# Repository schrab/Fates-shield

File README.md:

# Fates shield DAC board for Raspberry Pi

Monome [Fates](https://github.com/okyeron/fates) with MIDI and onboard microphone in Monome Shield form-factor

### Specs:

- WM8731 stereo audio codec with headphone driver
- Microphone
- ZJYM270-7PV2.0 SSD1325 128x64 OLED display (NHD-2.7-12864WDW3 alternative [from Aliexpress](https://aliexpress.ru/item/4000265549668.html))
  
- 3 pushbuttons
- 4 rotary encoders
- 2x 1/8in inputs
- 2x 1/8in outputs
- 1/8in stereo headphone out
- 1/8in UART MIDI in/out

###TODO
  
- [X] Fix upper OLED holes position
- [ ] Add RC filtering for encoders and keys
- [ ] Fix headphone jack hole
- [X] Fix swapped MIDI IN lines
- [X] Fix MIDI OUT buffer lines

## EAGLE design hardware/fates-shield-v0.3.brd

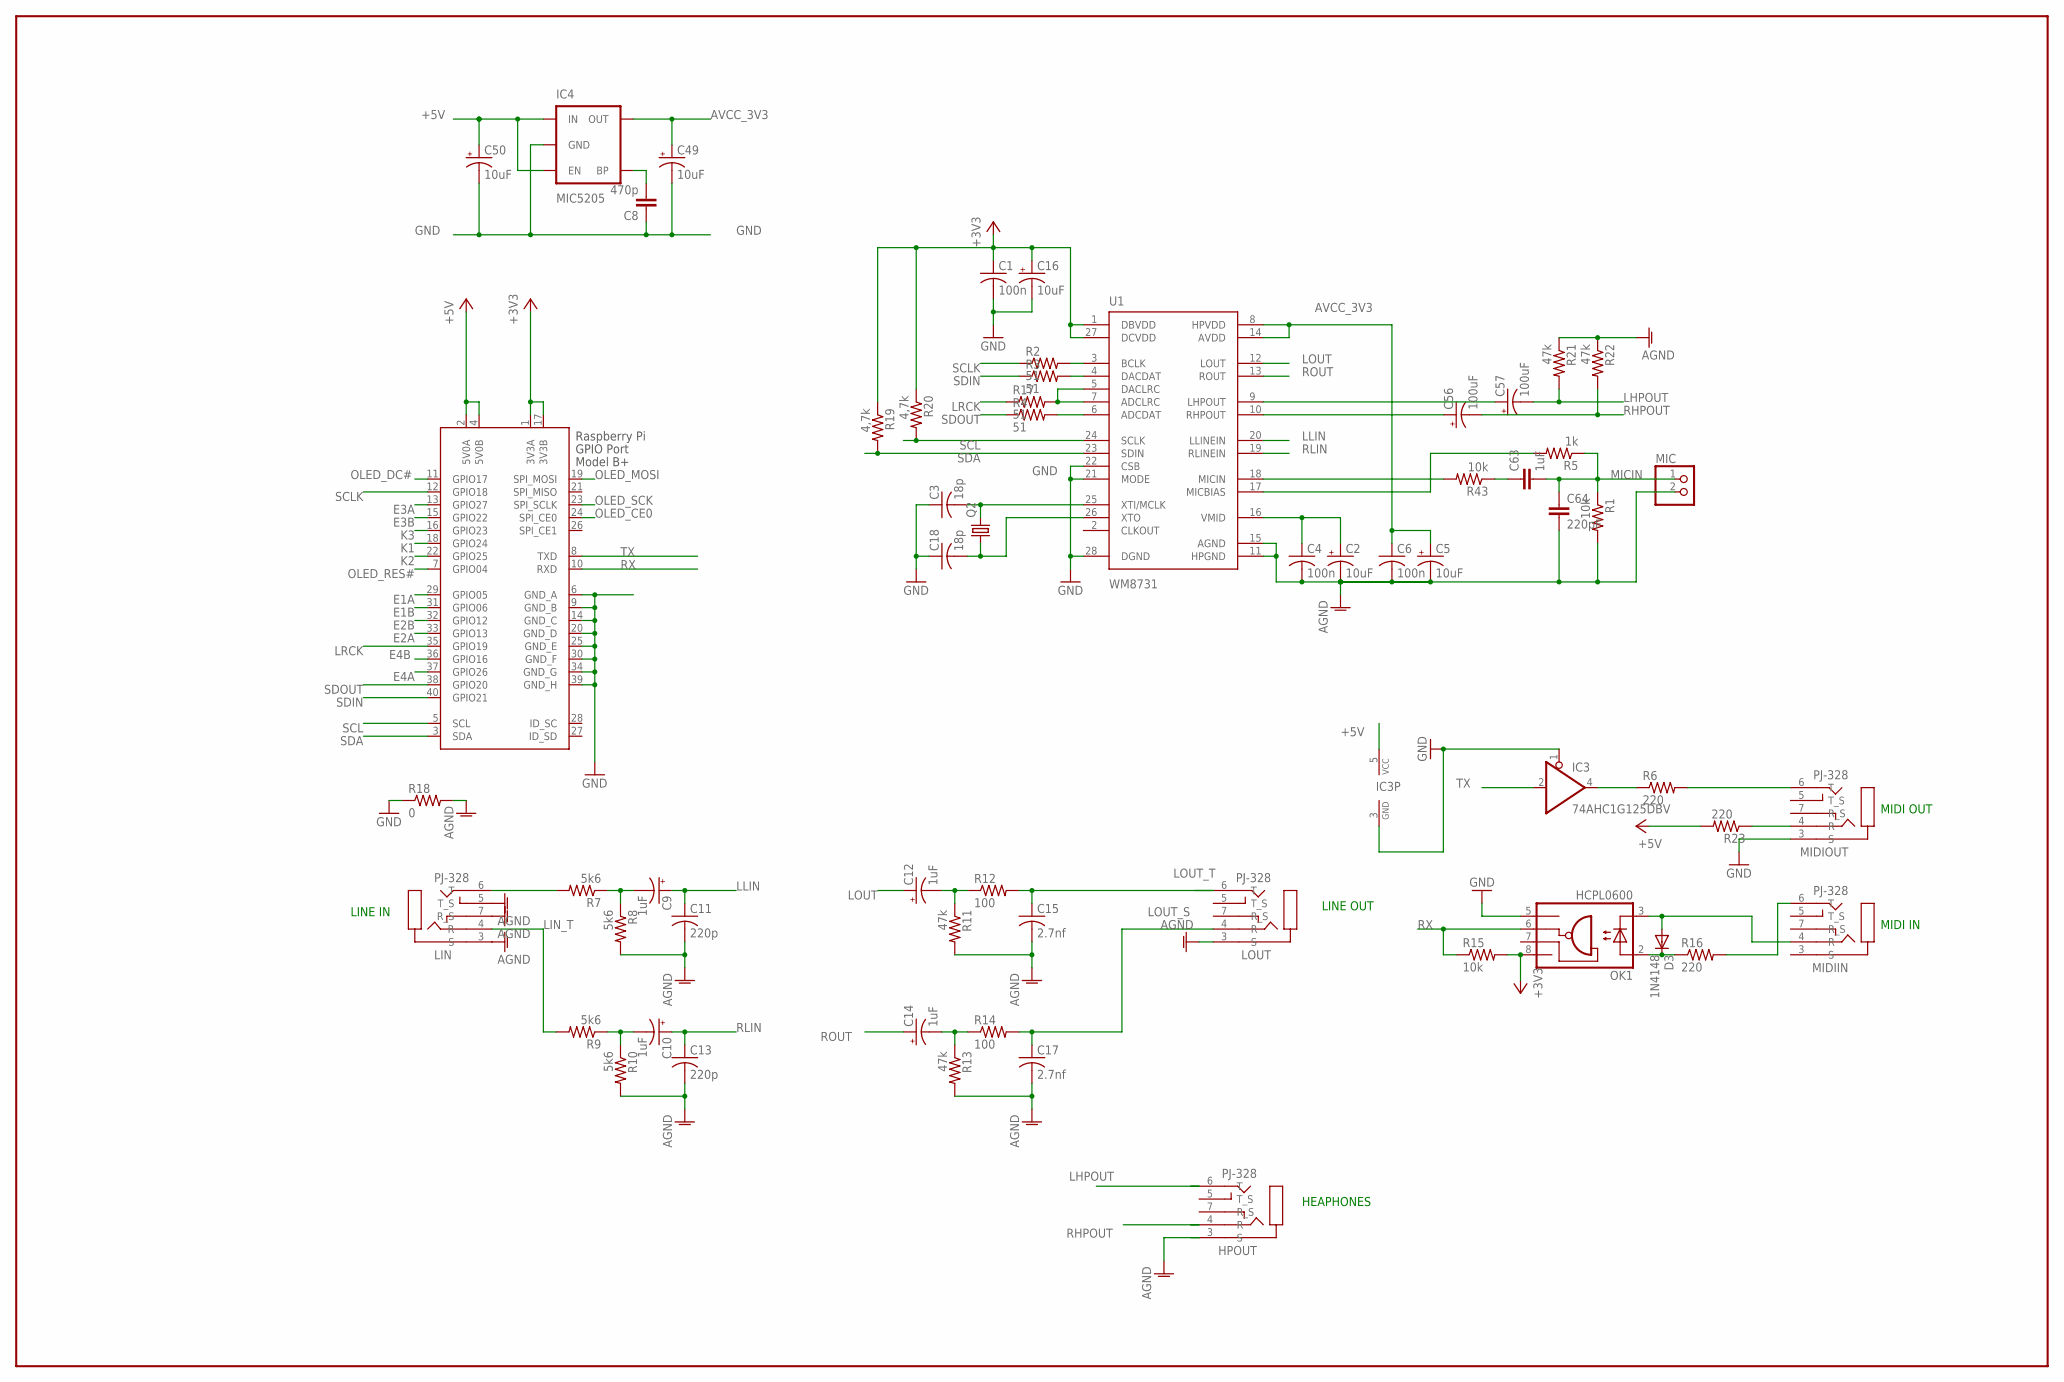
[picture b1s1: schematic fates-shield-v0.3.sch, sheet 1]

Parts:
C1, C4, C6: 100n; C0603
C2, C5, C16, C49, C50: 10uF; EIA3216
C3, C18: 18p; C0603
C8: 470p; 0603-CAP
C9, C10, C12, C14: 1uF; EIA3216
C11, C13: 220p; C0603
C15, C17: 2.7nf; C0603
C56, C57: 100uF; EIA3528
C63: 1uF; 0603-CAP
C64: 220pF; 0603-CAP
D3: 1N4148; SOD323-W
HPOUT: PJ-328; PJ328
IC3: 74AHC1G125DBV; DBV_R-PDSO-G5
IC4: MIC5205; SPARKFUN-3-2-07_SOT23-5
LIN: PJ-328; PJ328
LOUT: PJ-328; PJ328
MIC: PINHD-1X2; 1X02
MIDIIN: PJ-328; PJ328
MIDIOUT: PJ-328; PJ328
OK1: HCPL0600; SOIC08
Q2: CRYSTALHC49UP; HC49UP
R1, R43: 10k; 0603-RES
R2, R3, R4, R17: 51; R0603
R5: 1k; 0603-RES
R6, R16, R23: 220; R0603
R7, R8, R9, R10: 5k6; R0603
R11, R13: 47k; R0603
R12, R14: 100; R0603
R15: 10k; R0603
R18: 0; R0603
R19, R20: 4,7k; 0603-RES
R21, R22: 47k; 0603-RES
U1: WM8731; SSOP28
X1: RASPI_BOARD_B+#_E3; RASPI_BOARD_B+_EDGES_3DRILL

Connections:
+3V3: C1.1, C16.A (+), OK1.8 (VCC), R15.2, R19.1, R20.1, U1.1 (DBVDD), U1.27 (DCVDD), X1.1 (3V3A), X1.17 (3V3B); also elsewhere on the board
+5V: C50.A (+), IC3.5 (VCC), IC4.1 (IN), IC4.3 (EN), R23.2, X1.2 (5V0A), X1.4 (5V0B)
ADCDAT: R4.2, U1.6 (ADCDAT)
ADCLRC: R17.2, U1.5 (DACLRC), U1.7 (ADCLRC)
AGND: C2.C (-), C4.2, C5.C (-), C6.2, C11.2, C13.2, C15.2, C17.2, C64.2, HPOUT.3 (S), LIN.3 (S), LIN.5 (T_S), LIN.7 (R_S), LOUT.3 (S), MIC.2, R1.2, R8.2, R10.2, R11.2, R13.2, R18.2, R21.1, R22.1, U1.11 (HPGND), U1.15 (AGND)
AVCC_3V3: C5.A (+), C6.1, C49.A (+), IC4.5 (OUT), U1.8 (HPVDD), U1.14 (AVDD)
BCLK: R2.2, U1.3 (BCLK)
DACDAT: R3.2, U1.4 (DACDAT)
E1A: X1.29 (GPIO05); also elsewhere on the board
E1B: X1.31 (GPIO06); also elsewhere on the board
E2A: X1.33 (GPIO13); also elsewhere on the board
E2B: X1.32 (GPIO12); also elsewhere on the board
E3A: X1.13 (GPIO27); also elsewhere on the board
E3B: X1.15 (GPIO22); also elsewhere on the board
E4A: X1.37 (GPIO26); also elsewhere on the board
E4B: X1.36 (GPIO16); also elsewhere on the board
GND: C1.2, C3.1, C8.1, C16.C (-), C18.1, C49.C (-), C50.C (-), IC3.1 (OE), IC3.3 (GND), IC4.2 (GND), MIDIOUT.3 (S), OK1.5 (GND), R18.1, U1.21 (MODE), U1.22 (CSB), U1.28 (DGND), X1.6 (GND_A), X1.9 (GND_B), X1.14 (GND_C), X1.20 (GND_D), X1.25 (GND_E), X1.30 (GND_F), X1.34 (GND_G), X1.39 (GND_H); also elsewhere on the board
K1: X1.18 (GPIO24); also elsewhere on the board
K2: X1.22 (GPIO25); also elsewhere on the board
K3: X1.16 (GPIO23); also elsewhere on the board
LHPOUT: C57.C (-), HPOUT.6 (T), R21.2
LIN_T: LIN.4 (R), R9.2
LLIN: C9.A (+), C11.1, U1.20 (LLINEIN)
LOUT: C12.A (+), U1.12 (LOUT)
LOUT_S: C17.1, LOUT.4 (R), R14.2
LOUT_T: C15.1, LOUT.6 (T), R12.2
LRCK: R17.1, X1.35 (GPIO19)
L_HPOUT: C57.A (+), U1.9 (LHPOUT)
MICIN: C63.2, C64.1, MIC.1, R1.1, R5.1
MIC_BIAS: R5.2, U1.17 (MICBIAS)
MIC_IN: R43.2, U1.18 (MICIN)
unnamed: MIDIOUT.4 (R), R23.1
unnamed: IC3.4 (O), R6.1
unnamed: C2.A (+), C4.1, U1.16 (VMID)
unnamed: C9.C (-), R7.1, R8.1
unnamed: C10.C (-), R9.1, R10.1
unnamed: C14.C (-), R13.1, R14.1
unnamed: C12.C (-), R11.1, R12.1
unnamed: LIN.6 (T), R7.2
unnamed: D3.A, MIDIIN.4 (R), OK1.3 (C)
unnamed: D3.C, OK1.2 (A), R16.1
unnamed: MIDIIN.6 (T), R16.2
unnamed: MIDIOUT.6 (T), R6.2
unnamed: C8.2, IC4.4 (BP)
unnamed: C63.1, R43.1
OLED_CE0: X1.24 (SPI_CE0); also elsewhere on the board
OLED_DC#: X1.11 (GPIO17); also elsewhere on the board
OLED_MOSI: X1.19 (SPI_MOSI); also elsewhere on the board
OLED_RES#: X1.7 (GPIO04); also elsewhere on the board
OLED_SCK: X1.23 (SPI_SCLK); also elsewhere on the board
RHPOUT: C56.C (-), HPOUT.4 (R), R22.2
RLIN: C10.A (+), C13.1, U1.19 (RLINEIN)
ROUT: C14.A (+), U1.13 (ROUT)
RX: OK1.6 (VO), R15.1, X1.10 (RXD)
R_HPOUT: C56.A (+), U1.10 (RHPOUT)
SCL: R20.2, U1.24 (SCLK), X1.5 (SCL)
SCLK: R2.1, X1.12 (GPIO18)
SDA: R19.2, U1.23 (SDIN), X1.3 (SDA)
SDIN: R3.1, X1.40 (GPIO21)
SDOUT: R4.1, X1.38 (GPIO20)
TX: IC3.2 (I), X1.8 (TXD)
XTI: C3.2, Q2.2, U1.25 (XTI/MCLK)
XTO: C18.2, Q2.1, U1.26 (XTO)

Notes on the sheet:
MIDI OUT
MIDI IN
HEAPHONES
LINE OUT
LINE IN

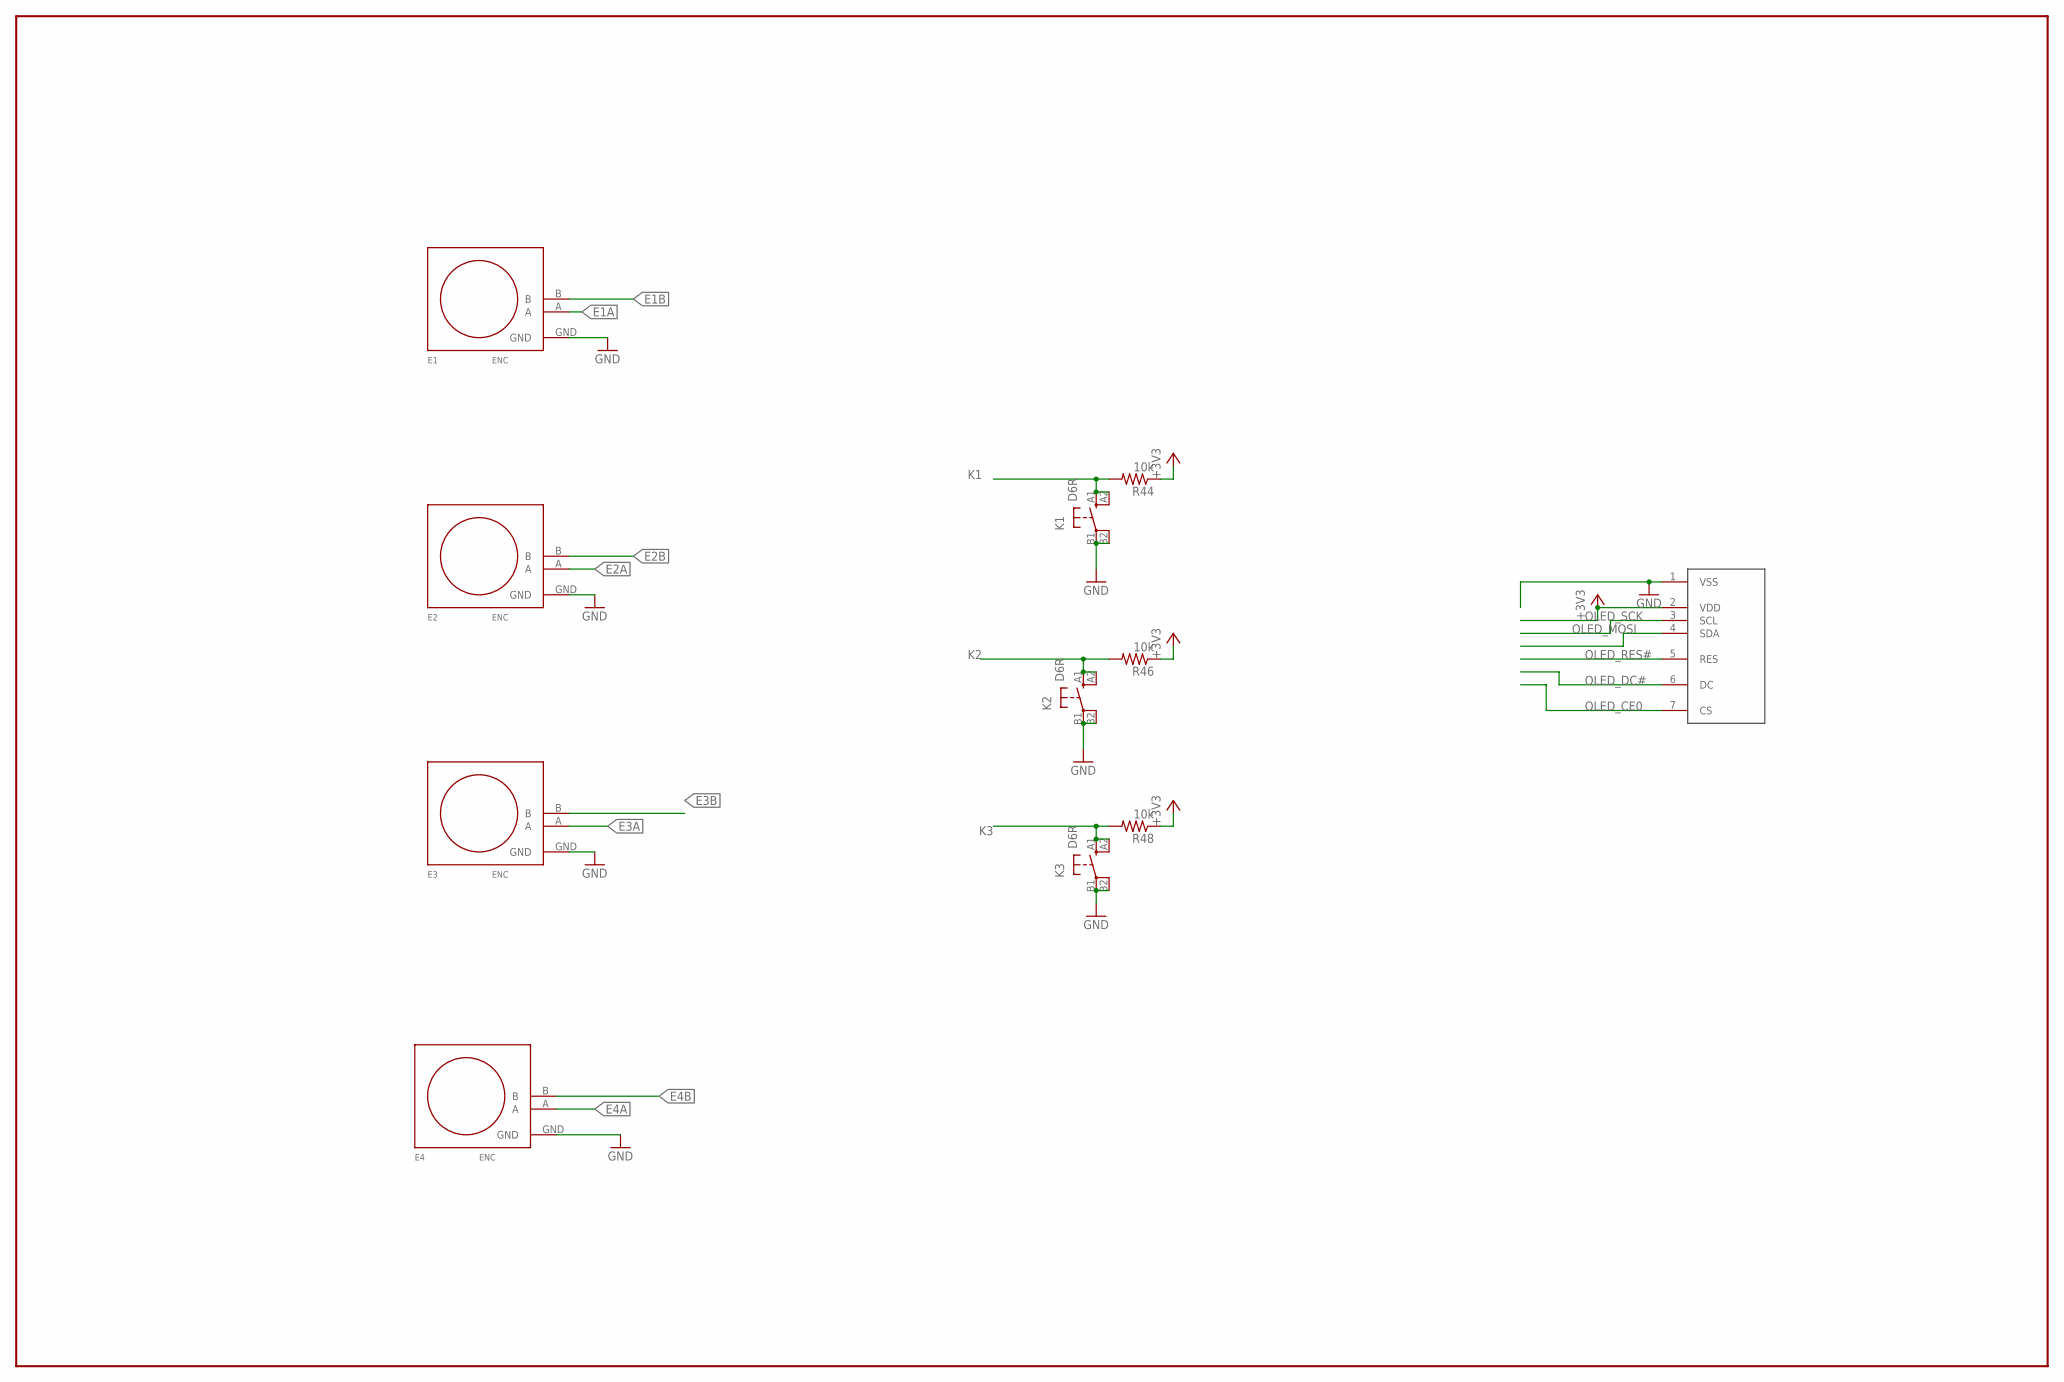
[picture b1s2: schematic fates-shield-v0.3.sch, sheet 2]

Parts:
E1, E2, E3, E4: ENC; PEC11RN
K1, K2, K3: D6R
R44, R46, R48: 10k; R0603
U$2: OLED128X64SSD1325; OLED-SSD1325

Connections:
+3V3: R44.1, R46.1, R48.1, U$2.2 (VDD); also elsewhere on the board
E1A: E1.A; also elsewhere on the board
E1B: E1.B; also elsewhere on the board
E2A: E2.A; also elsewhere on the board
E2B: E2.B; also elsewhere on the board
E3A: E3.A; also elsewhere on the board
E3B: E3.B; also elsewhere on the board
E4A: E4.A; also elsewhere on the board
E4B: E4.B; also elsewhere on the board
GND: E1.GND, E2.GND, E3.GND, E4.GND, K1.B1, K1.B2 (P1), K2.B1, K2.B2 (P1), K3.B1, K3.B2 (P1), U$2.1 (VSS); also elsewhere on the board
K1: K1.A1 (S), K1.A2 (S1), R44.2; also elsewhere on the board
K2: K2.A1 (S), K2.A2 (S1), R46.2; also elsewhere on the board
K3: K3.A1 (S), K3.A2 (S1), R48.2; also elsewhere on the board
OLED_CE0: U$2.7 (CS); also elsewhere on the board
OLED_DC#: U$2.6 (DC); also elsewhere on the board
OLED_MOSI: U$2.4 (SDA); also elsewhere on the board
OLED_RES#: U$2.5 (RES); also elsewhere on the board
OLED_SCK: U$2.3 (SCL); also elsewhere on the board

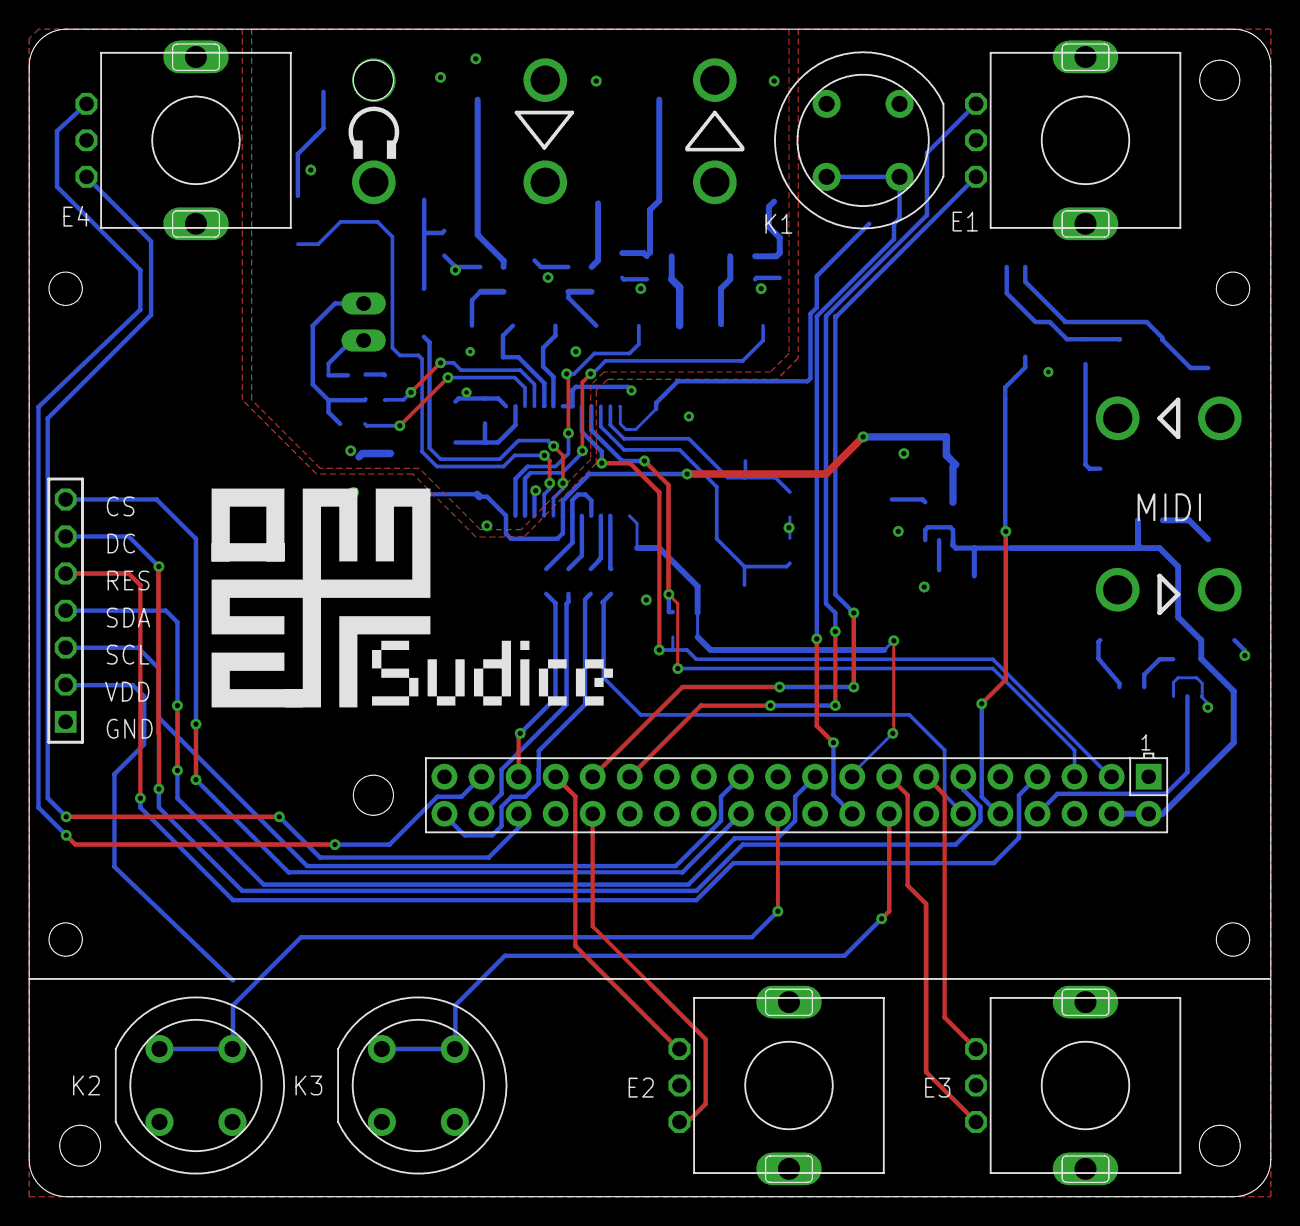
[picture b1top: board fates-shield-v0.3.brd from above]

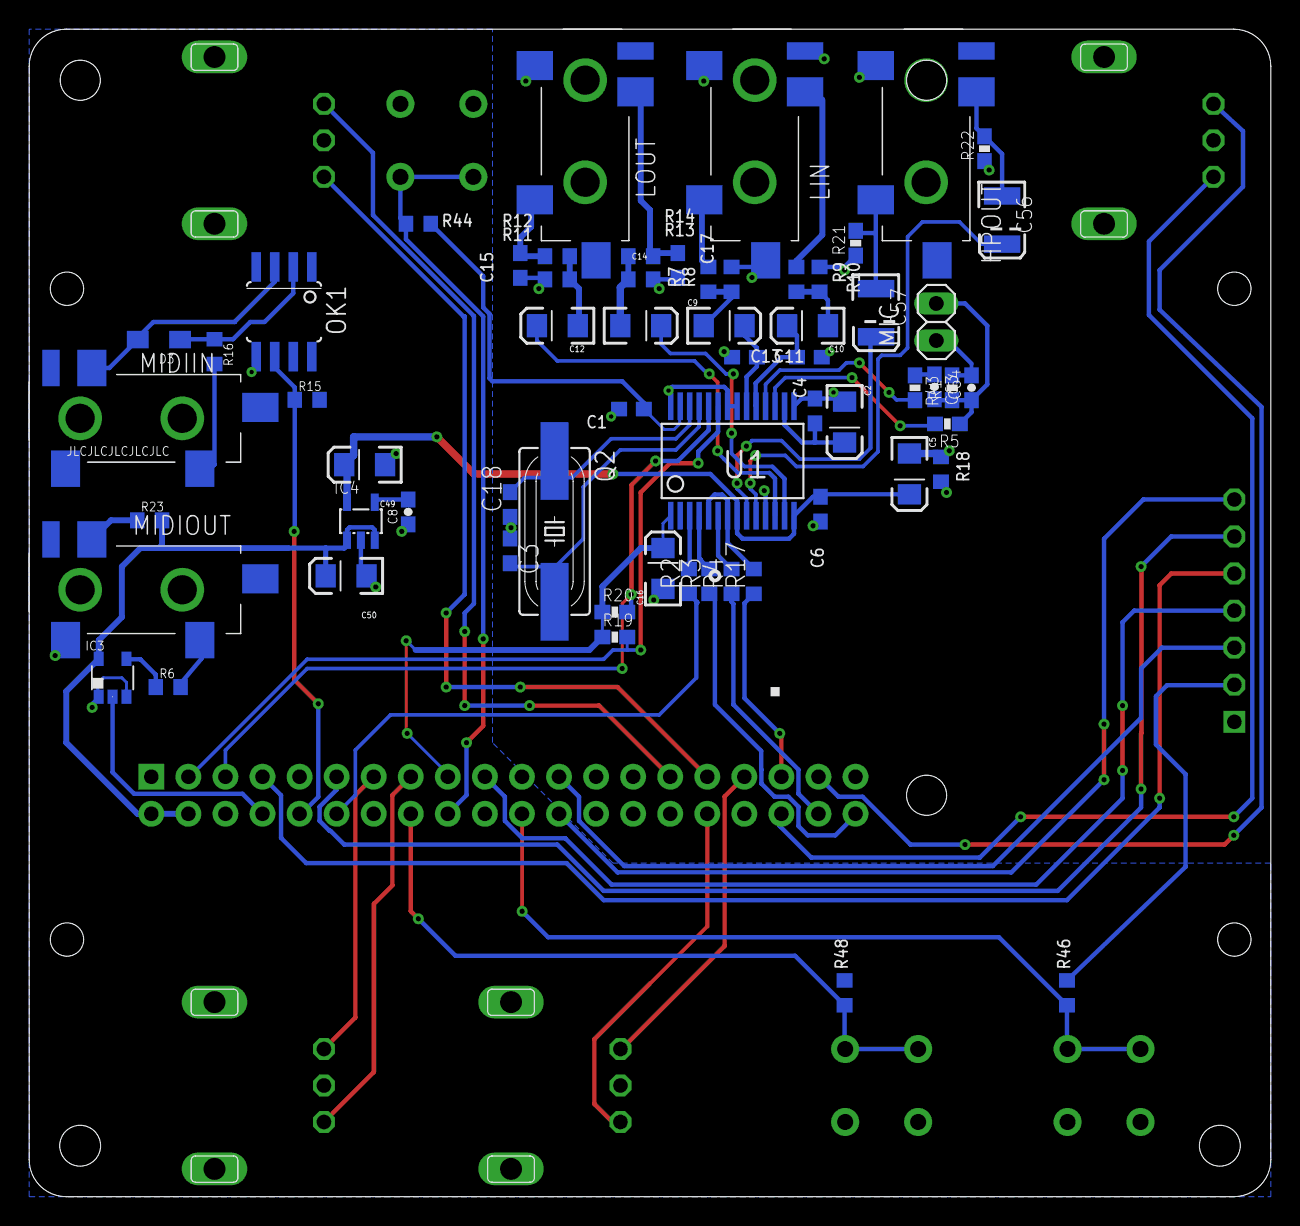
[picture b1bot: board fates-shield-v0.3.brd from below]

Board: 2 copper layers, 85.1 x 80.0 mm, 71 parts (62 on the bottom side), 63 nets.

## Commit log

2024-11-05 Schematic / Eagle files
